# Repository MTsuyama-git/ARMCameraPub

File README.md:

# ARMCameraPub
ARMCamera Repository(public version)

## pcb
基板の情報
## src
ファームウェア及び機能試作コード
DriverとMiddlewaresに関しては，STM32CubeMXで生成する必要があります．

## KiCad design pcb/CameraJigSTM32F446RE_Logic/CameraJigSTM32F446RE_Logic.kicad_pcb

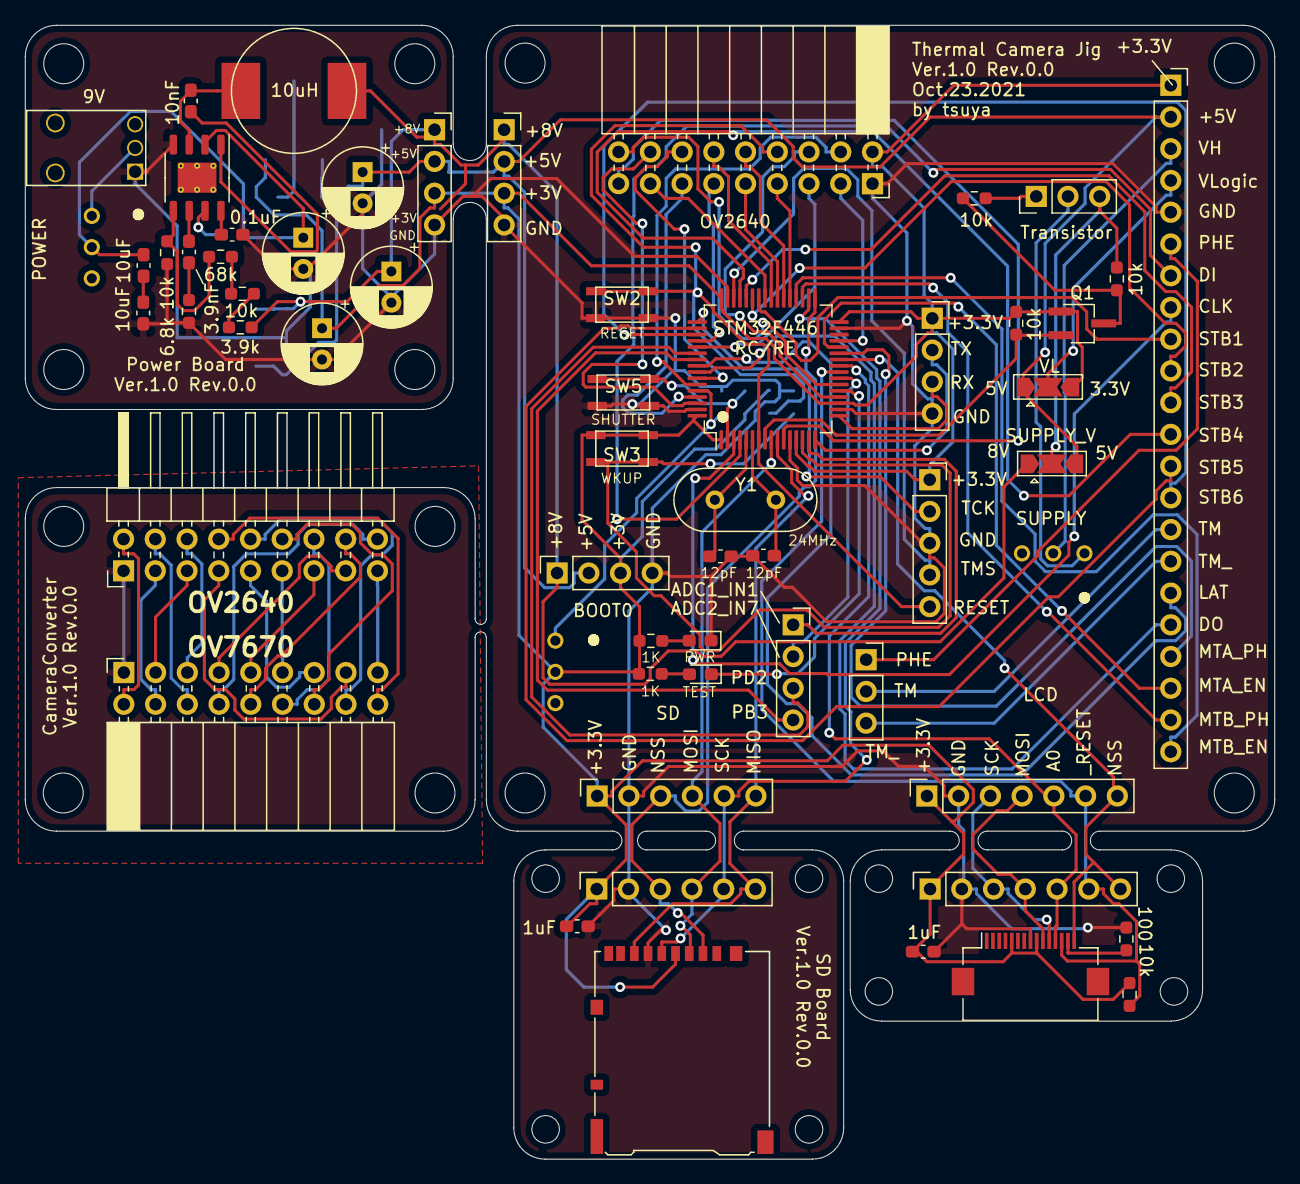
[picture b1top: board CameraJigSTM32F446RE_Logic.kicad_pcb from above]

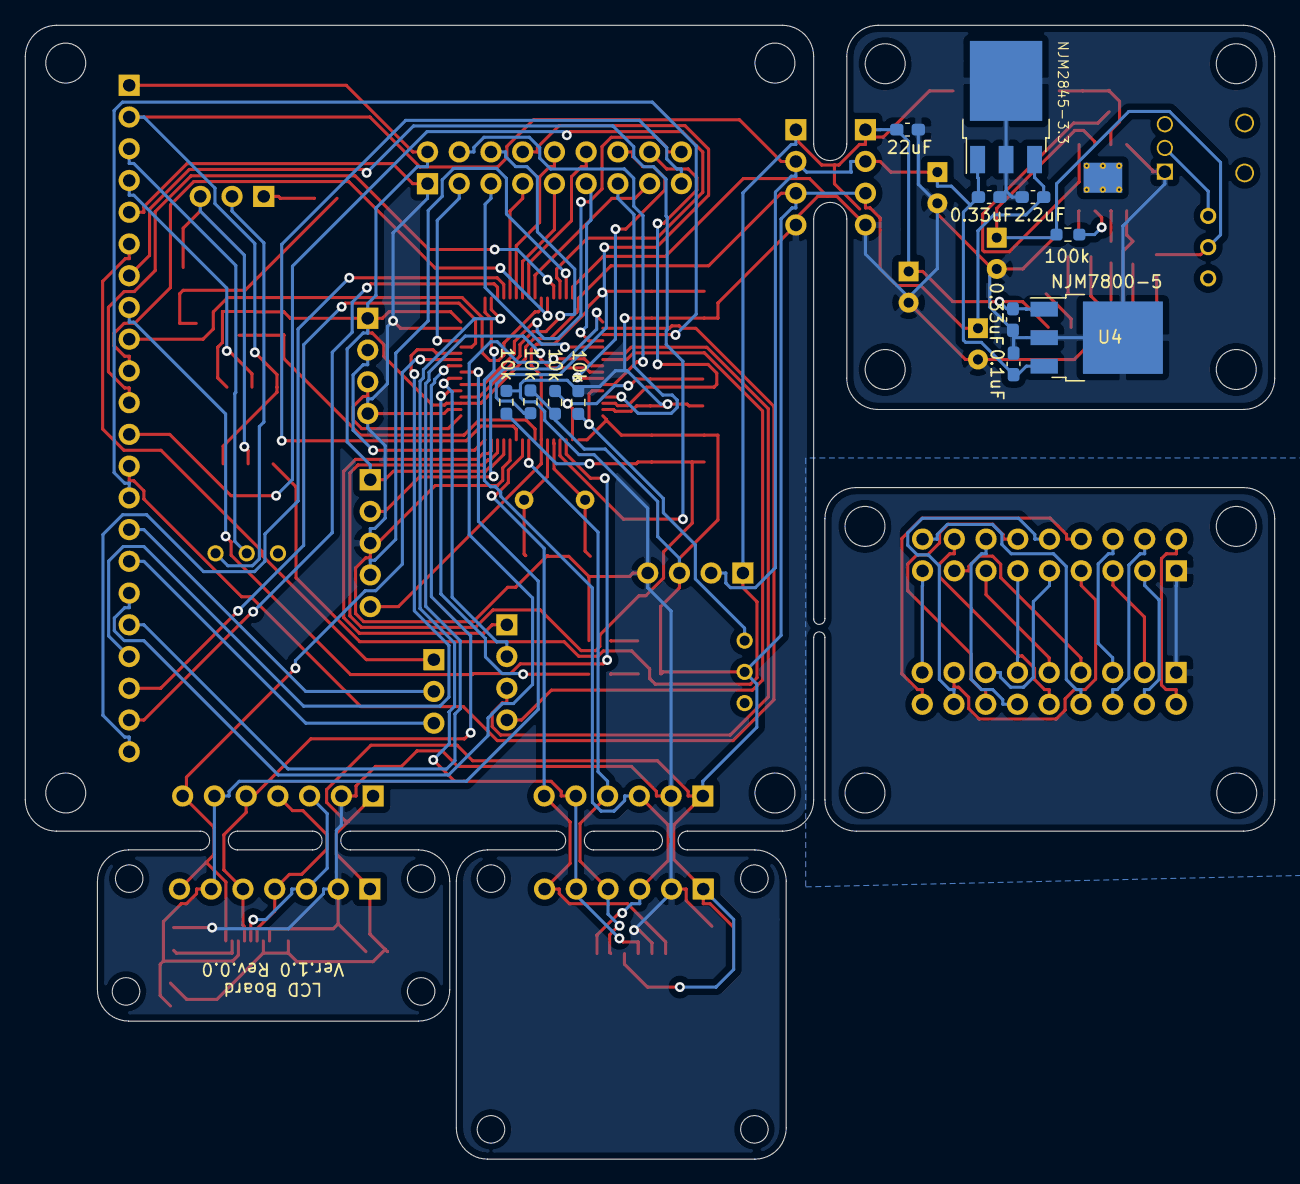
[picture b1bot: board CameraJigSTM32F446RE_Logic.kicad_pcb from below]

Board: 2 copper layers, 100.0 x 90.8 mm, 91 parts (12 on the bottom side), 100 nets.

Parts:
C1, C4, C5, C6: C; CP_Radial_D6.3mm_P2.50mm
C2, C3, C7, C8, C9, C10, C11, C12, C13, C14, C15, C16, C17, C18: C; C_0603_1608Metric_Pad1.08x0.95mm_HandSolder
D1, D2: LED; LED_0603_1608Metric_Pad1.05x0.95mm_HandSolder
J1: Conn_01x03_Female; PinSocket_1x03_P2.54mm_Vertical
J2: Conn_01x05_Female; PinSocket_1x05_P2.54mm_Vertical
J3: Conn_01x22_Female; PinSocket_1x22_P2.54mm_Vertical
J4, J17: Conn_01x04_Female; PinSocket_1x04_P2.54mm_Vertical
J5: Conn_01x03_Female; PinHeader_1x03_P2.54mm_Vertical
J6, J13: Conn_01x18_Female; PinSocket_2x09_P2.54mm_Horizontal
J8, J9, J21: Conn_01x05; PinSocket_1x04_P2.54mm_Vertical
J10, J11: Conn_01x06_Female; PinSocket_1x07_P2.54mm_Vertical
J12: Conn_01x18_Female; PinHeader_2x09_P2.54mm_Horizontal
J14, J15: Conn_01x06_Female; PinSocket_1x06_P2.54mm_Vertical
J16: Conn_01x09_Female; microSD_HC_Hirose_DM3AT-SF-PEJM5
J22, J23: Conn_01x03_Female; SolderJumper-3_P2.0mm_Open_TrianglePad1.0x1.5mm
L1: L; inductor_NR10050T100M
Q1: SMD-MOSFET-N-CH-50V-200MA-BSS138W-7-F_SOT-23_; TSOT-23_HandSoldering
R1, R2, R3, R4, R5, R6, R7, R14, R15, R32, R33, R34, R35, R36, R37, R38, R39: R; R_0603_1608Metric_Pad0.98x0.95mm_HandSolder
REF_0, REF_1, REF_2, REF_3, REF_4, REF_5, REF_6, REF_7, REF_8, REF_9: M3_margin6
REF_10, REF_11, REF_12, REF_13: M2_margin4_4
REF_a: M3_margin6
REF_b: M3_margin6
REF_c: M2_margin4_4
REF_d: M2_margin4_4
REF_e: M2_margin4_4
REF_f: M2_margin4_4
SW1, SW4, SW6: SW_DIP_x01; SW_2WAY
SW2, SW3, SW5: SW_DIP_x01; ALPS_SKRPABE010
U2: STM32F446RETx; LQFP-64_10x10mm_P0.5mm
U3: power_supply; POWER_Supply
U4, U6: SOT-89; TO-252-3_TabPin2
U5: MP2307; HSOP-8-1EP_3.9x4.9mm_P1.27mm_EP2.41x3.1mm_ThermalVias
U7: AE-ATM0177B3A; Hirose_FH12-15S-0.5SH_1x15-1MP_P0.50mm_Horizontal
Y1: Crystal; Crystal_HC49-4H_Vertical

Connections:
+3V3: C6.1, C15.1, C17.1, C18.1, J2.1, J3.1, J4.1, J6.2, J8.3, J9.3, J10.1, J11.1, J14.1, J15.1, J16.4, J21.3, J22.3, Q1.1, R1.2, R4.1, R5.1, R6.1, R14.1, R38.1, SW1.2, SW3.1, U2.1, U2.13, U2.19, U2.32, U2.48, U2.64, U6.3, U7.5, U7.9
+5V: C5.1, C11.1, C14.1, J3.2, J8.2, J9.2, J21.2, J22.1, J23.3, U4.3, U6.1
+8V: C4.1, C9.1, C16.1, J8.1, J9.1, J21.1, J23.1, L1.2, R37.1, U4.1
+9V: C1.1, C7.1, R32.1, SW6.2, U5.2
ADC1_IN1: J17.1, U2.15
ADC2_IN7: J17.2, U2.23
CAMERA_PWDN: J6.17, U2.11
CLK: J3.8, U2.3
DCMI_D0: J6.7, U2.37
DCMI_D1: J6.10, U2.38
DCMI_D2: J6.9, U2.39
DCMI_D3: J6.12, U2.40
DCMI_D4: J6.11, U2.52
DCMI_D5: J6.14, U2.58
DCMI_D6: J6.13, U2.61
DCMI_D7: J6.16, U2.62
DCMI_HSYNC: J6.6, U2.20
DCMI_PIXCLK: J6.18, U2.22
DCMI_VSYNC: J6.4, U2.59
DI: J3.7, U2.4
DO: J3.18, U2.57
GND: C1.2, C2.2, C3.2, C4.2, C5.2, C6.2, C8.2, C9.2, C11.2, C12.2, C14.2, C15.2, C16.2, C17.2, C18.2, D2.1, J2.3, J3.5, J4.4, J6.1, J8.4, J9.4, J10.2, J11.2, J14.2, J15.2, J16.6, J21.4, R2.2, R3.2, R33.2, R34.2, R39.1, SW2.1, SW5.1, U2.12, U2.18, U2.31, U2.47, U2.63, U3.2, U4.2, U5.4, U6.2, U7.8
HSUPPLY: Q1.3, R7.2, R15.2
I2C2_SCL: J6.3, U2.29
I2C2_SDA: J6.5, U2.53
LAT: J3.17, U2.56
LCD_A0: J10.5, J11.5, U2.25, U7.12
LCD_NSS: J10.7, J11.7, U2.26, U7.15
LCD_RESET: J10.6, J11.6, R38.2, U2.24, U7.13
LCD_SCK: J10.3, J11.3, U7.11
LD2: D1.1, U2.21
MTA_EN: J3.20, U2.28
MTA_PHASE: J3.19, U2.27
MTB_EN: J3.22, U2.36
MTB_PHASE: J3.21, U2.35
unnamed: C2.1, U2.5, Y1.1
unnamed: C3.1, U2.6, Y1.2
unnamed: C7.2, C8.1
unnamed: C10.1, U5.6
unnamed: C10.2, R33.1
unnamed: C12.1, U5.8
unnamed: C13.1, L1.1, U5.3
unnamed: C13.2, U5.1
unnamed: D1.2, R1.1
unnamed: D2.2, R5.2
unnamed: J5.1, R7.1
unnamed: J12.1, J13.1
unnamed: J12.2, J13.2
unnamed: J12.3, J13.4
unnamed: J12.4, J13.6
unnamed: J12.5, J13.3
unnamed: J12.6, J13.5
unnamed: J12.7, J13.15
unnamed: J12.8, J13.18
unnamed: J12.9, J13.13
unnamed: J12.10, J13.16
unnamed: J12.11, J13.11
unnamed: J12.12, J13.14
unnamed: J12.13, J13.9
unnamed: J12.14, J13.12
unnamed: J12.15, J13.7
unnamed: J12.16, J13.10
unnamed: J12.17, J13.17
unnamed: J12.18, J13.8
unnamed: R3.1, SW1.1, U2.60
unnamed: R32.2, U5.7
unnamed: R34.1, R35.2, U5.5
unnamed: R35.1, R36.2
unnamed: R36.1, R37.2
unnamed: R39.2, U7.14
unnamed: SW6.1, U3.1
PB3: J17.4, U2.55
PD2: J17.3, U2.54
PHE: J1.1, J3.6
RCC_MCO_1: J6.15, U2.41
RESET: J2.5, J6.8, R4.2, SW2.2, U2.7
SD_NSS: J14.3, J15.3, J16.2, U2.33
SHUTTER: R6.2, SW5.2, U2.2
SPI2_MISO: J14.6, J15.6, J16.7, U2.10
SPI2_MOSI: J14.4, J15.4, J16.3, U2.9
SPI2_SCK: J14.5, J15.5, J16.5, U2.34
SPI_MOSI: J10.4, J11.4, U7.10
STB1: J3.9, U2.42
STB2: J3.10, U2.43
STB3: J3.11, U2.44
STB4: J3.12, U2.45
STB5: J3.13, U2.50
STB6: J3.14, U2.51
SUPPLY: Q1.2, R14.2, U2.8
SUPPLY_OUT: J5.2, SW4.1
SUPPLY_V: J5.3, J23.2, R15.1
SYS_WKUP0: R2.1, SW3.2, U2.14
TCK: J2.2, U2.49
TM: J1.2, J3.15
TMS: J2.4, U2.46
TM_: J1.3, J3.16
USART2_RX: J4.3, U2.17
USART2_TX: J4.2, U2.16
VH: J3.3, SW4.2
VLOGIC: J3.4, J22.2

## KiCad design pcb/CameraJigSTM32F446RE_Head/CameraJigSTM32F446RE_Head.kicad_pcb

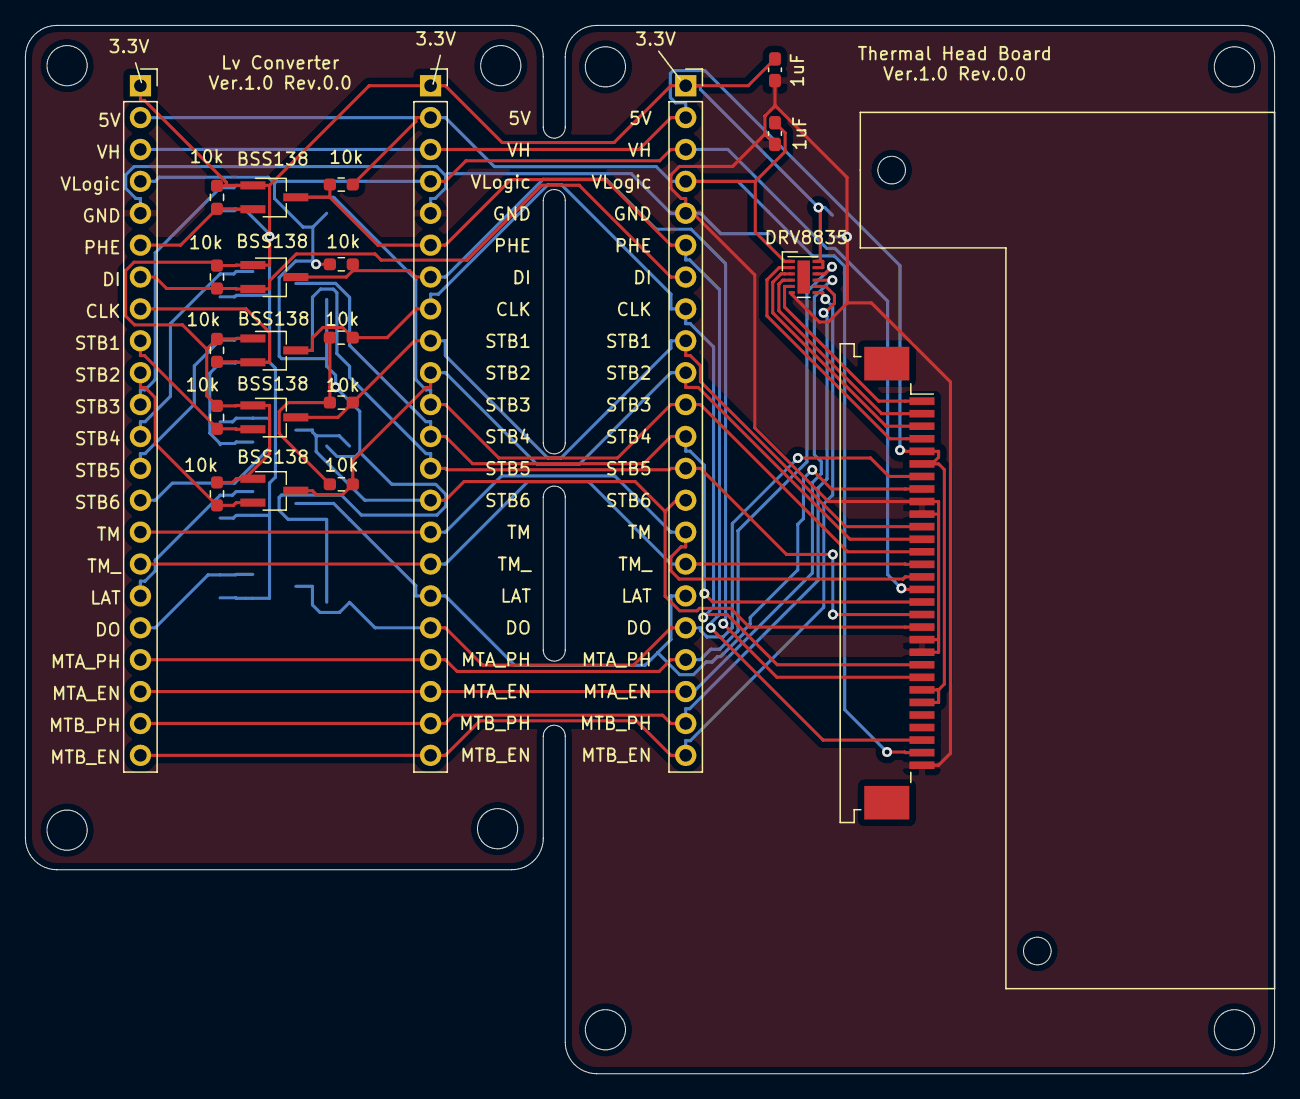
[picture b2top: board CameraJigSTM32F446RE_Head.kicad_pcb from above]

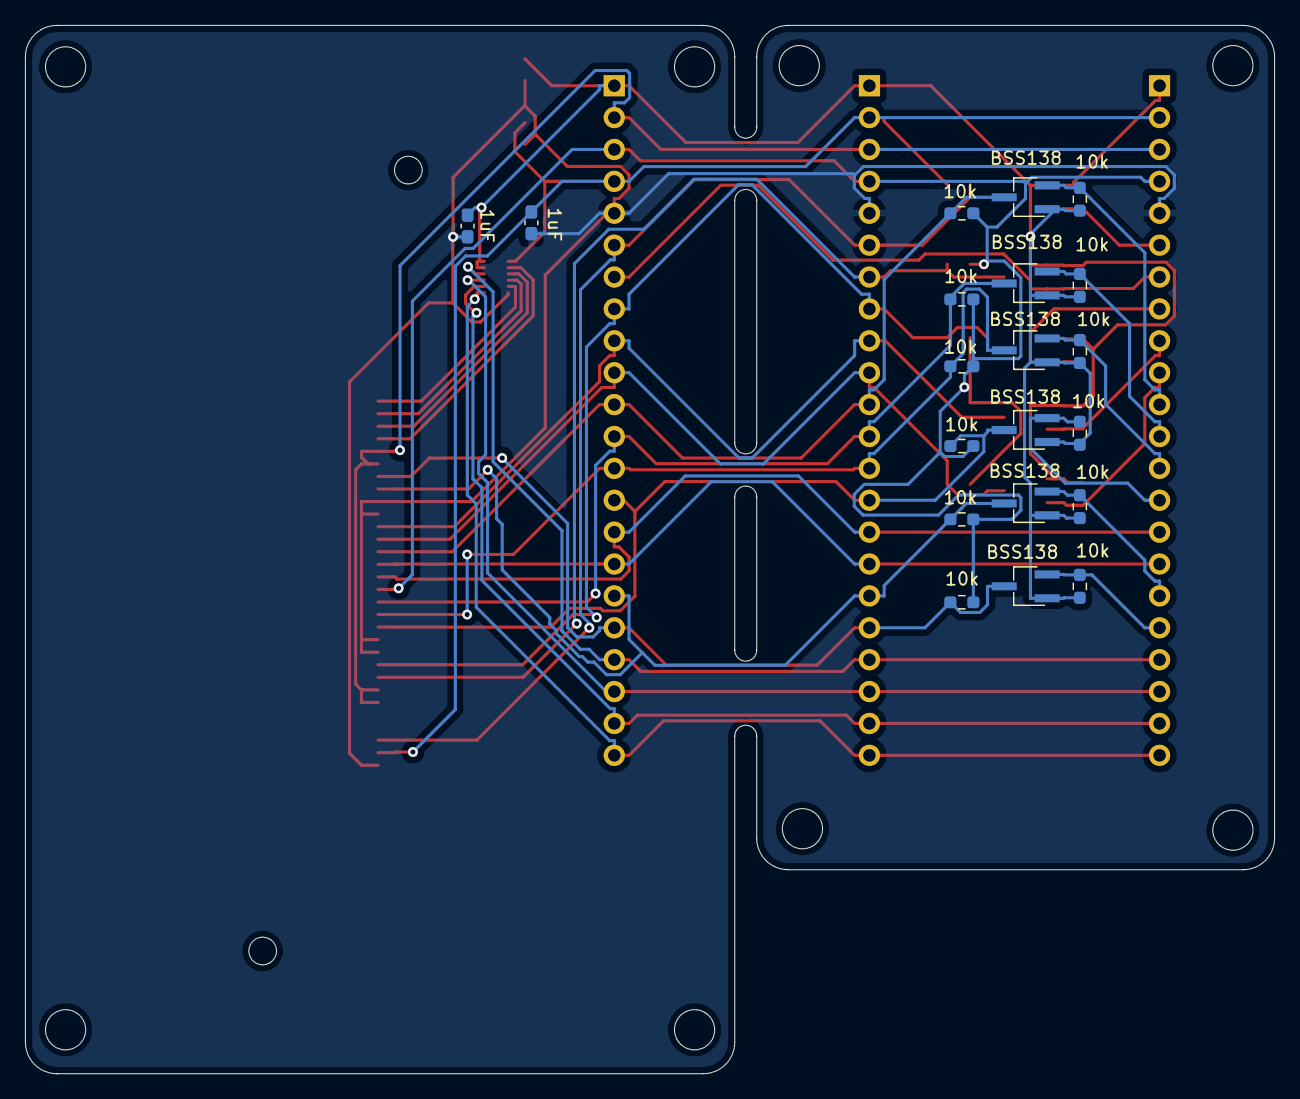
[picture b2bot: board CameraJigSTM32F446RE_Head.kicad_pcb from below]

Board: 2 copper layers, 99.5 x 83.5 mm, 51 parts (20 on the bottom side), 37 nets.

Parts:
C1, C2, C3, C4: C; C_0603_1608Metric_Pad1.08x0.95mm_HandSolder
J1, J3, J4: Conn_01x22_Female; PinSocket_1x22_P2.54mm_Vertical
J2: Conn_01x30_Female; TE_3-84952-0_1x30-1MP_P1.0mm_Horizontal
Q1, Q2, Q3, Q4, Q5, Q6, Q7, Q8, Q9, Q10, Q11: SMD-MOSFET-N-CH-50V-200MA-BSS138W-7-F_SOT-23_; TSOT-23_HandSoldering
R1, R2, R3, R4, R5, R6, R7, R8, R9, R10, R11, R12, R13, R14, R15, R16, R17, R18, R19, R20, R21, R22: R; R_0603_1608Metric_Pad0.98x0.95mm_HandSolder
REF_0, REF_1, REF_2, REF_3, REF_4, REF_5, REF_6, REF_7: M3_margin6
REF_head: thermal_printer_head
U1: DRV8835; WSON-12-1EP_3x2mm_P0.5mm_EP1x2.65

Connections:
+3V3: C3.2, C4.1, J1.1, J3.1, J4.1, Q1.1, Q2.1, Q3.1, Q4.1, Q5.1, Q6.1, Q7.1, Q8.1, Q9.1, Q10.1, Q11.1, R1.1, R3.1, R4.1, R5.1, R6.1, R7.1, R8.1, R9.1, R17.1, R18.1, R19.1, U1.11, U1.12
+5V: C1.1, C2.1, J1.4, J2.29, J3.2, J4.2, R2.1, U1.1
CLK: J3.8, Q10.2, R18.2
DI: J1.7, J3.7, Q7.2, R8.2
DO: J3.18, Q11.2, R19.2
GND: C1.2, C2.2, C3.1, C4.2, J1.5, J2.9, J2.10, J2.20, J2.21, J2.30, J3.5, J4.5, U1.6
HCLK: J1.8, J2.22, J4.8, Q10.3, R21.2
HDI: J2.23, J4.7, Q7.3, R15.2
HDO: J1.18, J2.7, J4.18, Q11.3, R22.2
HLAT: J1.17, J2.8, J4.17, Q9.3, R20.2
HMTA: J2.4, U1.2
HMTB: J2.2, U1.4
HMT_A: J2.3, U1.3
HMT_B: J2.1, U1.5
HPHE: J1.6, J2.28, J4.6, Q1.3, R2.2
HSTB1: J1.9, J2.11, J4.9, Q8.3, R16.2
HSTB2: J1.10, J2.12, J4.10, Q6.3, R14.2
HSTB3: J1.11, J2.13, J4.11, Q4.3, R12.2
HSTB4: J1.12, J2.17, J4.12, Q2.3, R10.2
HSTB5: J1.13, J2.18, J4.13, Q5.3, R13.2
HSTB6: J1.14, J2.19, J4.14, Q3.3, R11.2
LAT: J3.17, Q9.2, R17.2
MTA_EN: J1.20, J3.20, J4.20, U1.9
MTA_PHASE: J1.19, J3.19, J4.19, U1.10
MTB_EN: J1.22, J3.22, J4.22, U1.7
MTB_PHASE: J1.21, J3.21, J4.21, U1.8
PHE: J3.6, Q1.2, R1.2
STB1: J3.9, Q8.2, R9.2
STB2: J3.10, Q6.2, R7.2
STB3: J3.11, Q4.2, R5.2
STB4: J3.12, Q2.2, R3.2
STB5: J3.13, Q5.2, R6.2
STB6: J3.14, Q3.2, R4.2
TM: J1.15, J2.15, J3.15, J4.15
TM_: J1.16, J2.14, J3.16, J4.16
VH: J1.2, J2.5, J2.6, J2.24, J2.25, J3.3, J4.3
VLOGIC: J1.3, J2.16, J3.4, J4.4, R10.1, R11.1, R12.1, R13.1, R14.1, R15.1, R16.1, R20.1, R21.1, R22.1

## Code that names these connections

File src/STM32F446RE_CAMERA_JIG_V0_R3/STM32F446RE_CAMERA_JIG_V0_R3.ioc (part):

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Mcu.Name=STM32F446R(C-E)Tx
Mcu.Package=LQFP64
Mcu.UserName=STM32F446RETx
PA0-WKUP.Mode=SYS_WakeUp0
PA0-WKUP.Signal=SYS_WKUP0
PA1.Signal=ADCx_IN1
PA10.GPIOParameters=GPIO_Label
PA10.GPIO_Label=STB2
PA10.Signal=GPIO_Output
PA11.GPIOParameters=GPIO_Label
PA11.GPIO_Label=STB3
PA11.Signal=GPIO_Output
PA12.GPIOParameters=GPIO_Label
PA12.GPIO_Label=STB4
PA12.Signal=GPIO_Output
PA13.GPIOParameters=GPIO_Label
PA13.GPIO_Label=TMS
PA13.Mode=Serial_Wire
PA13.Signal=SYS_JTMS-SWDIO
PA14.GPIOParameters=GPIO_Label
PA14.GPIO_Label=TCK
PA14.Mode=Serial_Wire
PA14.Signal=SYS_JTCK-SWCLK
PA15.GPIOParameters=GPIO_Label
PA15.GPIO_Label=STB5
PA15.Signal=GPIO_Output
PA2.GPIOParameters=GPIO_Label
PA2.GPIO_Label=USART_TX
PA2.Mode=Asynchronous
PA2.Signal=USART2_TX
PA3.GPIOParameters=GPIO_Label
PA3.GPIO_Label=USART_RX
PA3.Mode=Asynchronous
PA3.Signal=USART2_RX
PA4.Mode=Slave_8_bits_External_Synchro
PA4.Signal=DCMI_HSYNC
PA5.GPIOParameters=GPIO_Label
PA5.GPIO_Label=LD2 [Green Led]
PA5.Signal=GPIO_Output
PA6.Mode=Slave_8_bits_External_Synchro
PA6.Signal=DCMI_PIXCLK
PA7.Signal=ADCx_IN7
PA8.Mode=Clock-out-1
PA8.Signal=RCC_MCO_1
PA9.GPIOParameters=GPIO_Label
PA9.GPIO_Label=STB1
PA9.Signal=GPIO_Output
PB0.GPIOParameters=GPIO_Label
PB0.GPIO_Label=LCD_NSS
PB0.Signal=GPIO_Output
PB1.GPIOParameters=GPIO_Label
PB1.GPIO_Label=MTA_PHASE
PB1.Signal=GPIO_Output
PB10.Mode=I2C
PB10.Signal=I2C2_SCL
PB12.GPIOParameters=GPIO_Label
PB12.GPIO_Label=SD_NSS
PB12.Signal=GPIO_Output
PB13.Mode=Full_Duplex_Master
PB13.Signal=SPI2_SCK
PB14.GPIOParameters=GPIO_Label
PB14.GPIO_Label=MTB_PHASE
PB14.Signal=GPIO_Output
PB15.GPIOParameters=GPIO_Label
PB15.GPIO_Label=MTB_EN
PB15.Signal=GPIO_Output
PB2.GPIOParameters=GPIO_Label
PB2.GPIO_Label=MTA_EN
PB2.Signal=GPIO_Output
PB3.GPIOParameters=GPIO_Label
PB3.GPIO_Label=SWO
PB3.Signal=SYS_JTDO-SWO
PB4.GPIOParameters=GPIO_Label
PB4.GPIO_Label=LAT
PB4.Signal=GPIO_Output
PB5.Signal=GPIO_Input
PB6.Mode=Slave_8_bits_External_Synchro
PB6.Signal=DCMI_D5
PB7.Mode=Slave_8_bits_External_Synchro
PB7.Signal=DCMI_VSYNC
PB8.Mode=Slave_8_bits_External_Synchro
PB8.Signal=DCMI_D6
PB9.Mode=Slave_8_bits_External_Synchro
PB9.Signal=DCMI_D7
PC0.GPIOParameters=GPIO_Label
PC0.GPIO_Label=SUPPLY
PC0.Signal=GPIO_Output
PC1.Mode=Full_Duplex_Master
PC1.Signal=SPI2_MOSI
PC10.GPIOParameters=GPIO_Label
PC10.GPIO_Label=STB6
PC10.Signal=GPIO_Output
PC11.Mode=Slave_8_bits_External_Synchro
PC11.Signal=DCMI_D4
PC12.Mode=I2C
PC12.Signal=I2C2_SDA
PC13.GPIOParameters=GPIO_Label,GPIO_ModeDefaultEXTI
PC13.GPIO_Label=B1 [Blue PushButton]
PC13.GPIO_ModeDefaultEXTI=GPIO_MODE_IT_FALLING
PC13.Signal=GPXTI13
PC14-OSC32_IN.GPIOParameters=GPIO_Label
PC14-OSC32_IN.GPIO_Label=CLK
PC14-OSC32_IN.Signal=GPIO_Output
PC15-OSC32_OUT.GPIOParameters=GPIO_Label
PC15-OSC32_OUT.GPIO_Label=DI
PC15-OSC32_OUT.Signal=GPIO_Output
PC2.Mode=Full_Duplex_Master
PC2.Signal=SPI2_MISO
PC3.GPIOParameters=GPIO_Label
PC3.GPIO_Label=CAMERA_PWDN
PC3.Signal=GPIO_Output
PC4.GPIOParameters=GPIO_Label
PC4.GPIO_Label=LCD_RESET
PC4.Signal=GPIO_Output
PC5.GPIOParameters=GPIO_Label
PC5.GPIO_Label=LCD_A0
PC5.Signal=GPIO_Output
PC6.Mode=Slave_8_bits_External_Synchro
PC6.Signal=DCMI_D0
PC7.Mode=Slave_8_bits_External_Synchro
PC7.Signal=DCMI_D1
PC8.Mode=Slave_8_bits_External_Synchro
PC8.Signal=DCMI_D2
PC9.Mode=Slave_8_bits_External_Synchro
PC9.Signal=DCMI_D3
PH0-OSC_IN.Mode=HSE-External-Oscillator
PH0-OSC_IN.Signal=RCC_OSC_IN
PH1-OSC_OUT.Mode=HSE-External-Oscillator
PH1-OSC_OUT.Signal=RCC_OSC_OUT
RCC.HSE_VALUE=24000000
RCC.SYSCLKFreq_VALUE=24000000
RCC.SYSCLKSource=RCC_SYSCLKSOURCE_HSE
board=NUCLEO-F446RE
boardIOC=true

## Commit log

2022-01-27 added source codes
